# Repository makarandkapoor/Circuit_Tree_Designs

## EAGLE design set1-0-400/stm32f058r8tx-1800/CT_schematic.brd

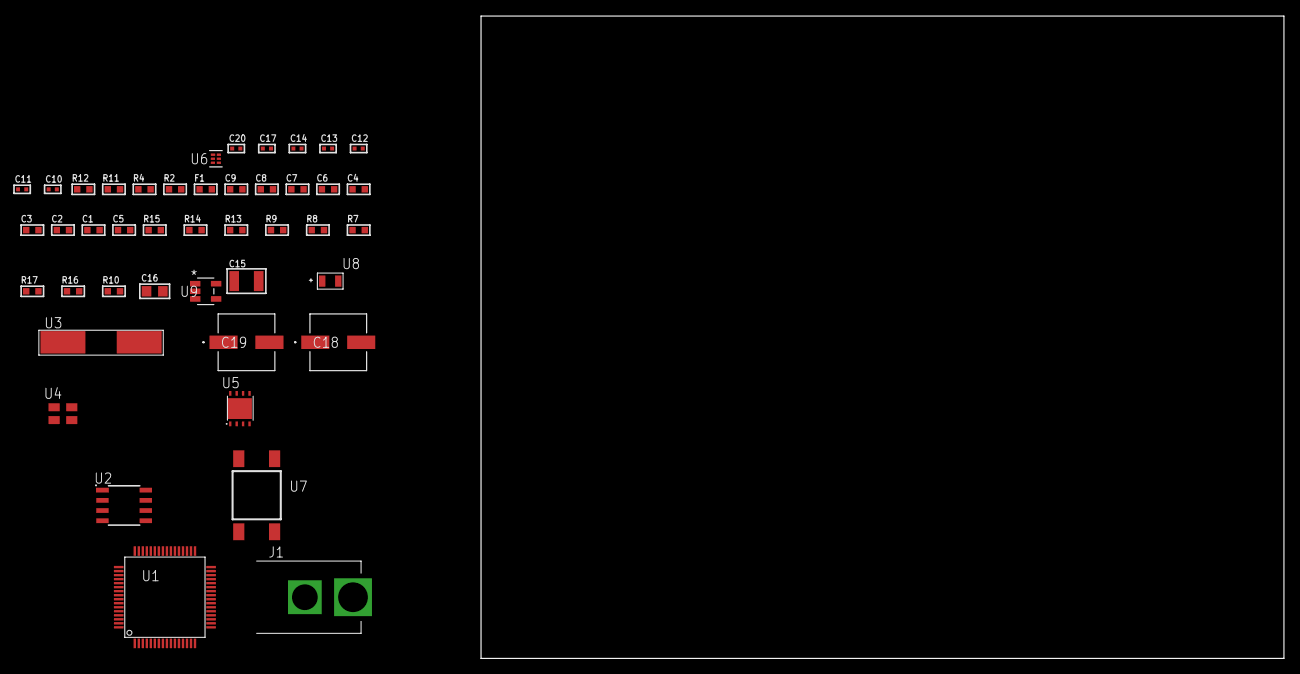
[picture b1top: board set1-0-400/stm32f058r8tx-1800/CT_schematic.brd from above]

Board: 2 copper layers, 100.0 x 80.0 mm, 44 parts (0 on the bottom side), 19 nets, no tracks yet.

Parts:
C1, C9: 1e-06; C0603
C2, C3, C4, C6, C7: 1e-07; C0603
C5: 4.7e-06; C0603
C8: 1e-08; C0603
C10, C11: 1e-11; C0402
C12, C13, C14, C20: 1e-08; C0402
C15: 1e-05; C1210
C16: 1e-05; C0805
C17: 1e-07; C0402
C18, C19: 0.0001; EXV-9H
F1: 240.0; L0603
J1: PJ-037B; PJ-037B_PACKAGE
R2, R12: 1000.0; R0603
R4: 4700.0; R0603
R7, R8, R9, R13, R14: 10000.0; R0603
R10: 100000.0; R0603
R11: 806.0; R0603
R15: 82000.0; R0603
R16: 300000.0; R0603
R17: 120000.0; R0603
U1: stm32f058r8t7; LQFP64
U2: M24M02-DRMN6TP; SOIC-8
U3: ABLS-25.000MHZ-B2F-T
U4: ASEK-2-32.768KHz-ECST; ASEK
U5: LP3878SDX-ADJ/NOPB; WSON-8
U6: TPS3895ADRYR; SON-6
U7: 4-1437565-2; SW_4-1437565-2
U8: Q65110A2395; LGM67K-G1J2-24-Z
U9: nc7sz125m5x; NC7SZ125M5X

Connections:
CLK_CRYSTAL_U1_5: C10.1, U1.5, U3.1
CLK_CRYSTAL_U1_6: C11.1, U1.6, U3.2
CLK_U1_3: U1.3, U4.3
GND: C1.2, C2.2, C3.2, C4.2, C5.2, C6.2, C7.2, C8.2, C9.2, C10.2, C11.2, C12.2, C13.2, C14.2, C15.2, C16.2, C17.2, C18.2, C19.2, C20.2, J1.2, R2.2, R7.2, R8.2, R9.2, R12.2, R15.2, R17.2, U1.12, U1.31, U1.63, U2.4, U4.2, U5.3, U5.PAD, U6.2, U8.C, U9.1, U9.3
NET_U1_7: R4.1, U1.7, U9.4
NET_U1_13: C8.1, C9.1, F1.1, U1.13
NET_U1_28: R8.1, U1.28
NET_U1_60: R7.1, U1.60
NET_U1_62: U7.3, U7.4
NET_U2_3: R9.1, U2.3
NET_U5_1: C14.1, U5.1
NET_U5_6: R11.2, R12.1, U5.6
NET_U5_8: R10.1, U5.8
NET_U6_1: R14.1, R15.1, U6.1
NET_U6_3: R16.2, R17.1, U6.3
NET_U6_4: R13.1, U6.4, U9.2
NET_U7_1: R2.1, U7.1, U7.2
VCC_S1_13V7: C15.1, C18.1, C19.1, J1.1, R10.2, U5.4
VCC_TIER1_1V8: C1.1, C2.1, C3.1, C4.1, C5.1, C6.1, C7.1, C12.1, C13.1, C16.1, C17.1, C20.1, F1.2, R4.2, R11.1, R13.2, R14.2, R16.1, U1.1, U1.32, U1.64, U2.8, U4.4, U5.5, U6.6, U9.5

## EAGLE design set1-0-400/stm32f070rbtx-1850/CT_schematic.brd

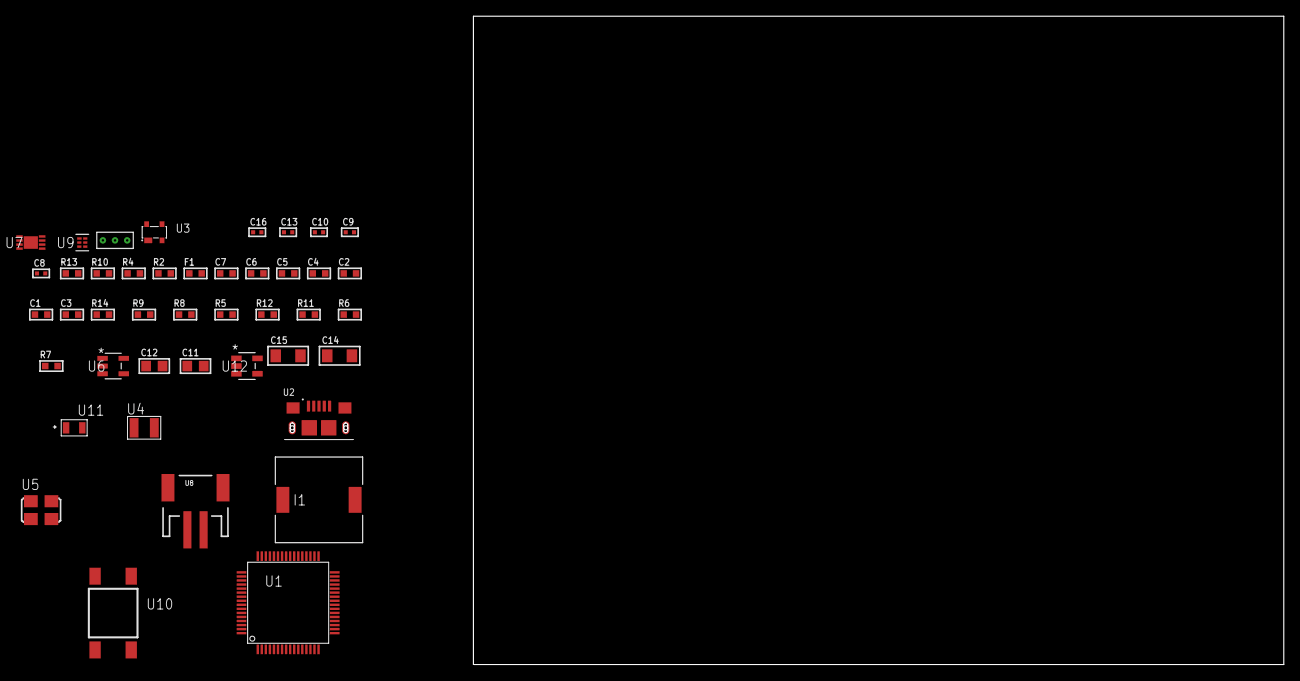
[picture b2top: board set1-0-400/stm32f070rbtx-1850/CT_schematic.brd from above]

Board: 2 copper layers, 122.6 x 80.0 mm, 43 parts (0 on the bottom side), 24 nets, no tracks yet.

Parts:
C1, C2, C4, C5: 1e-07; C0603
C3: 4.7e-06; C0603
C6: 1e-08; C0603
C7: 1e-06; C0603
C8, C9: 1e-11; C0402
C10, C16: 1e-08; C0402
C11, C12: 1e-05; C0805
C13: 1e-07; C0402
C14, C15: 1e-05; C1206
F1: 240.0; L0603
I1: 2.5e-06; DR1040
R2: 1000.0; R0603
R4: 4700.0; R0603
R5, R8, R9, R14: 10000.0; R0603
R6: 220000.0; R0603
R7: 1000000.0; R0603
R10: 9100.0; R0603
R11: 680000.0; R0603
R12: 120000.0; R0603
R13: 2000.0; R0603
U1: stm32f070rbt7; LQFP64
U2: 10118193-0001LF; FCI_10118193-0001LF
U3: prtr5v0u2ax; SOT143B
U4: ABS07-32.768KHZ-7-T
U5: ASFL1-25MHZ-NCS; ASFL1
U6: ltc3406es5; TSOT-23-5
U7: MCP73831T-2ACI/MC; DFN8_2X3MC
U8: S2B-PH-SM4-TB(LF)(SN); JST-2-SMD
U9: TPS3895ADRYR; SON-6
U10: 4-1437565-2; SW_4-1437565-2
U11: Q65110A2395; LGM67K-G1J2-24-Z
U12: nc7sz125m5x; NC7SZ125M5X
U13: Dummy; DUMMY_PACKAGE_90

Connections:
CLK_CRYSTAL_U1_3: C8.1, U1.3, U4.1
CLK_CRYSTAL_U1_4: C9.1, U1.4, U4.2
CLK_U1_5: U1.5, U5.3
GND: C1.2, C2.2, C3.2, C4.2, C5.2, C6.2, C7.2, C8.2, C9.2, C10.2, C11.2, C12.1, C12.2, C13.2, C14.2, C15.2, C16.2, R2.2, R5.2, R6.2, R10.2, R12.2, R13.2, U1.12, U1.18, U1.31, U1.47, U1.63, U2.5, U2.6, U2.7, U2.8, U2.9, U3.1, U5.2, U6.2, U7.6, U7.9, U8.2, U9.2, U11.C, U12.1, U12.3, U13.1
INPUT_USBPOWER_5V: C14.1, R14.2, U2.1, U3.4, U7.1, U7.2
NET_U1_7: R4.1, U1.7, U12.4
NET_U1_13: C6.1, C7.1, F1.1, U1.13
NET_U1_60: R5.1, U1.60
NET_U1_62: U10.3, U10.4
NET_U6_3: I1.1, U6.3
NET_U6_5: R6.1, R7.1, U6.5
NET_U6_ATNET_3: I1.2, R7.2
NET_U7_5: R14.1, U7.5
NET_U7_8: R13.1, U7.8
NET_U9_1: R9.1, R10.1, U9.1
NET_U9_3: R11.2, R12.1, U9.3
NET_U9_4: R8.1, U9.4, U12.2
NET_U10_1: R2.1, U10.1, U10.2
PROC_ADC_IN0: U1.14, U13.2
PROC_ADC_IN1: U1.15, U13.3
PROC_USB_DM: U1.44, U2.2, U3.3
PROC_USB_DP: U1.45, U2.3, U3.2
VCC_S1_3V7: C11.1, C15.1, U6.4, U7.3, U7.4, U8.1
VCC_TIER1_3V3: C1.1, C2.1, C3.1, C4.1, C5.1, C10.1, C12.2, C13.1, C16.1, F1.2, I1.2, R4.2, R7.2, R8.2, R9.2, R11.1, U1.1, U1.19, U1.32, U1.48, U1.64, U5.4, U9.6, U12.5

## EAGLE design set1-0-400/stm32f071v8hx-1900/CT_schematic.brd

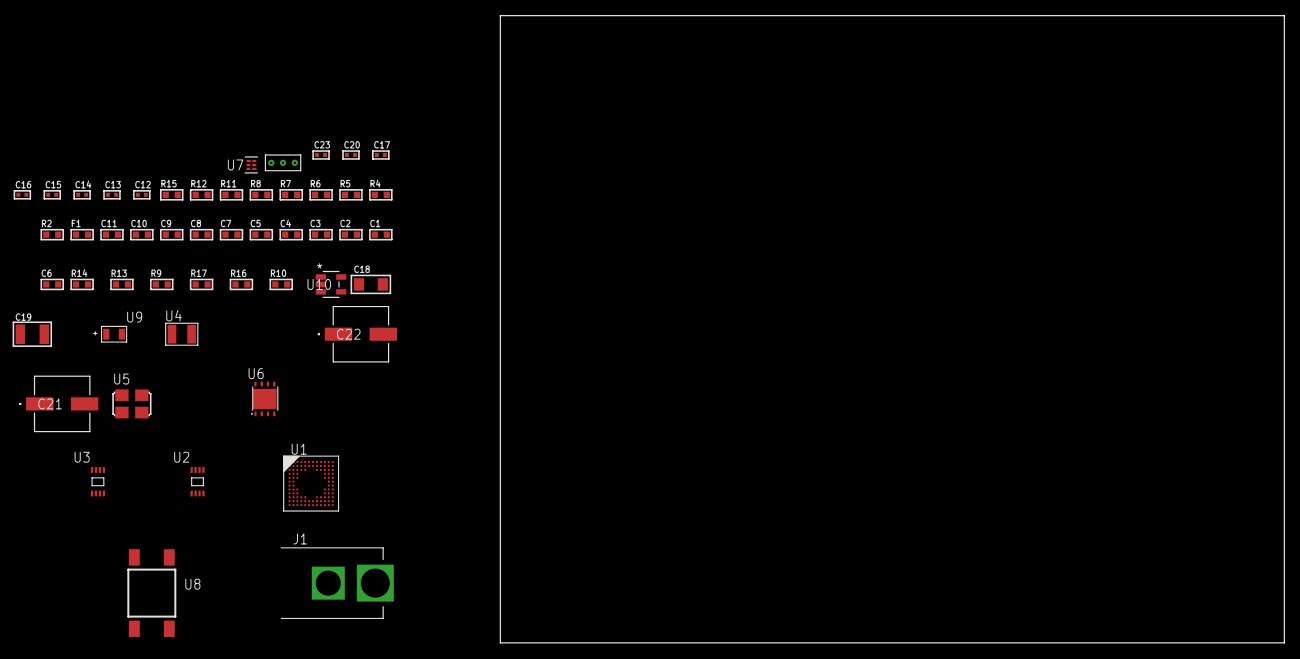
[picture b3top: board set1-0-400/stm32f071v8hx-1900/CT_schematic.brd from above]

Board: 2 copper layers, 100.0 x 80.0 mm, 51 parts (0 on the bottom side), 23 nets, no tracks yet.

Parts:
C1, C11: 1e-06; C0603
C2, C3, C4, C5, C7, C8, C9: 1e-07; C0603
C6: 4.7e-06; C0603
C10: 1e-08; C0603
C12, C13: 1e-11; C0402
C14, C15, C16, C17, C23: 1e-08; C0402
C18: 1e-05; C1206
C19: 1e-05; C1210
C20: 1e-07; C0402
C21, C22: 0.0001; EXV-9H
F1: 240.0; L0603
J1: PJ-037B; PJ-037B_PACKAGE
R2, R12: 1000.0; R0603
R4: 4700.0; R0603
R5, R6, R7, R8: 2200.0; R0603
R9, R13, R14: 10000.0; R0603
R10: 100000.0; R0603
R11: 2231.0; R0603
R15: 9100.0; R0603
R16: 680000.0; R0603
R17: 120000.0; R0603
U1: stm32f071v8h6; UFBGA100
U2: 24AA01T-I/MNY; TDFN-8/6MM
U3: 24AA04-I/MC; TDFN-8/6MM
U4: ABS07-32.768KHZ-7-T
U5: ASFL1-25MHZ-NCS; ASFL1
U6: LP3878SDX-ADJ/NOPB; WSON-8
U7: TPS3895ADRYR; SON-6
U8: 4-1437565-2; SW_4-1437565-2
U9: Q65110A2395; LGM67K-G1J2-24-Z
U10: nc7sz125m5x; NC7SZ125M5X
U11: Dummy; DUMMY_PACKAGE_112

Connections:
CLK_CRYSTAL_U1_D1: C12.1, U1.D1, U4.1
CLK_CRYSTAL_U1_E1: C13.1, U1.E1, U4.2
CLK_U1_F1: U1.F1, U5.3
GND: C1.2, C2.2, C3.2, C4.2, C5.2, C6.2, C7.2, C8.2, C9.2, C10.2, C11.2, C12.2, C13.2, C14.2, C15.2, C16.2, C17.2, C18.2, C19.2, C20.2, C21.2, C22.2, C23.2, J1.2, R2.2, R9.2, R12.2, R15.2, R17.2, U1.D3, U1.F11, U1.F12, U1.K1, U2.4, U3.4, U3.7, U5.2, U6.3, U6.PAD, U7.2, U9.C, U10.1, U10.3, U11.1
NET_U1_A3: R5.1, U1.A3, U2.6
NET_U1_A4: R9.1, U1.A4
NET_U1_B3: R6.1, U1.B3, U2.5
NET_U1_H2: R4.1, U1.H2, U10.4
NET_U1_K11: R8.1, U1.K11, U3.5
NET_U1_K12: R7.1, U1.K12, U3.6
NET_U1_M1: C10.1, C11.1, F1.1, U1.M1
NET_U1_M12: U8.3, U8.4
NET_U6_1: C17.1, U6.1
NET_U6_6: R11.2, R12.1, U6.6
NET_U6_8: R10.1, U6.8
NET_U7_1: R14.1, R15.1, U7.1
NET_U7_3: R16.2, R17.1, U7.3
NET_U7_4: R13.1, U7.4, U10.2
NET_U8_1: R2.1, U8.1, U8.2
PROC_TIM1_CH2: U1.D10, U11.2
PROC_TIM1_CH4: U1.B12, U11.3
VCC_S1_11V0: C18.1, C21.1, C22.1, J1.1, R10.2, U6.4
VCC_TIER1_3V3: C1.1, C2.1, C3.1, C4.1, C5.1, C6.1, C7.1, C8.1, C9.1, C14.1, C15.1, C16.1, C19.1, C20.1, C23.1, F1.2, R4.2, R5.2, R6.2, R7.2, R8.2, R11.1, R13.2, R14.2, R16.1, U1.C4, U1.E2, U1.G11, U1.G12, U1.H3, U2.7, U2.8, U3.8, U5.4, U6.5, U7.6, U10.5

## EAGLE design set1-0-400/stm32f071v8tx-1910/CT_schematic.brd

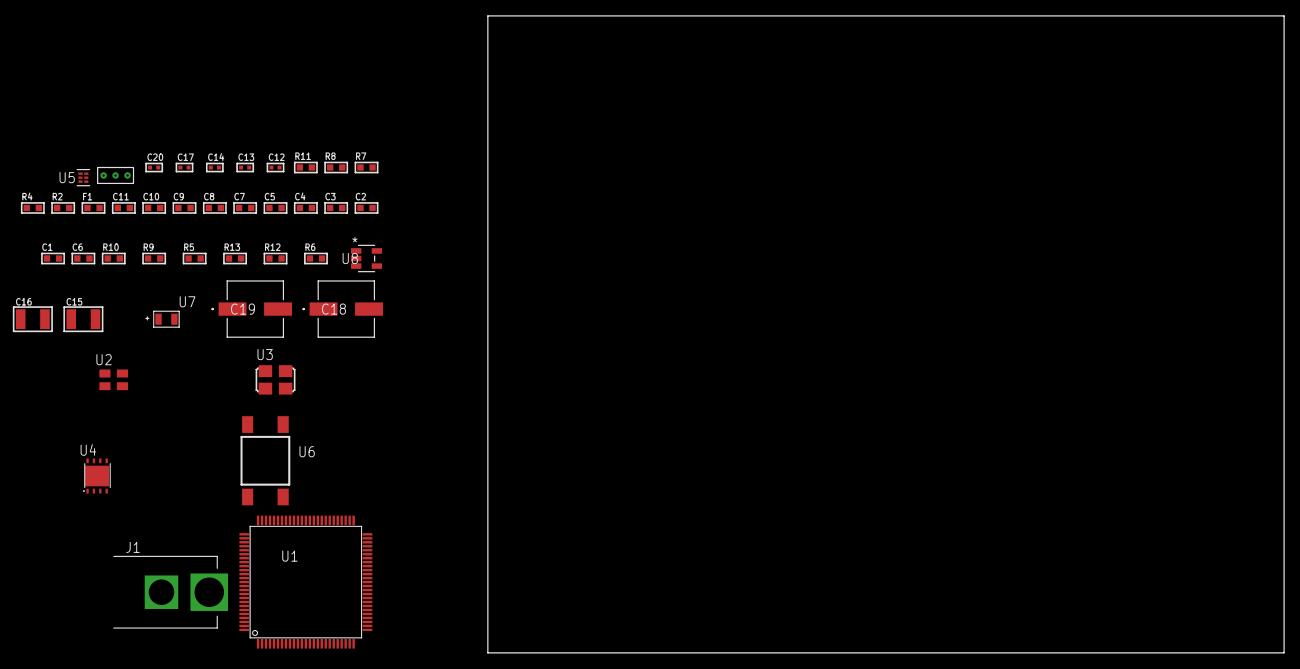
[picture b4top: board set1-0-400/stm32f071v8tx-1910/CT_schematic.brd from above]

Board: 2 copper layers, 100.0 x 80.0 mm, 42 parts (0 on the bottom side), 18 nets, no tracks yet.

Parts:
C1, C11: 1e-06; C0603
C2, C3, C4, C5, C7, C8, C9: 1e-07; C0603
C6: 4.7e-06; C0603
C10: 1e-08; C0603
C12, C13, C14, C20: 1e-08; C0402
C15, C16: 1e-05; C1210
C17: 1e-07; C0402
C18, C19: 0.0001; EXV-9H
F1: 240.0; L0603
J1: PJ-037B; PJ-037B_PACKAGE
R2, R8: 1000.0; R0603
R4: 4700.0; R0603
R5, R9, R10: 10000.0; R0603
R6: 100000.0; R0603
R7: 2231.0; R0603
R11: 9100.0; R0603
R12: 680000.0; R0603
R13: 120000.0; R0603
U1: stm32f071v8t6; LQFP100
U2: ASEK-32.768KHz-ECST; ASEK
U3: ASFL1-25MHZ-NCS; ASFL1
U4: LP3878SDX-ADJ/NOPB; WSON-8
U5: TPS3895ADRYR; SON-6
U6: 4-1437565-2; SW_4-1437565-2
U7: Q65110A2395; LGM67K-G1J2-24-Z
U8: nc7sz125m5x; NC7SZ125M5X
U9: Dummy; DUMMY_PACKAGE_89

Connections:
CLK_U1_8: U1.8, U2.3
CLK_U1_12: U1.12, U3.3
GND: C1.2, C2.2, C3.2, C4.2, C5.2, C6.2, C7.2, C8.2, C9.2, C10.2, C11.2, C12.2, C13.2, C14.2, C15.2, C16.2, C17.2, C18.2, C19.2, C20.2, J1.2, R2.2, R5.2, R8.2, R11.2, R13.2, U1.20, U1.27, U1.49, U1.74, U1.99, U2.2, U3.2, U4.3, U4.PAD, U5.2, U7.C, U8.1, U8.3, U9.1
NET_U1_14: R4.1, U1.14, U8.4
NET_U1_21: C10.1, C11.1, F1.1, U1.21
NET_U1_94: R5.1, U1.94
NET_U1_98: U6.3, U6.4
NET_U4_1: C14.1, U4.1
NET_U4_6: R7.2, R8.1, U4.6
NET_U4_8: R6.1, U4.8
NET_U5_1: R10.1, R11.1, U5.1
NET_U5_3: R12.2, R13.1, U5.3
NET_U5_4: R9.1, U5.4, U8.2
NET_U6_1: R2.1, U6.1, U6.2
PROC_PE2: U1.1, U9.2
PROC_PE3: U1.2, U9.3
VCC_S1_13V4: C15.1, C18.1, C19.1, J1.1, R6.2, U4.4
VCC_TIER1_3V3: C1.1, C2.1, C3.1, C4.1, C5.1, C6.1, C7.1, C8.1, C9.1, C12.1, C13.1, C16.1, C17.1, C20.1, F1.2, R4.2, R7.1, R9.2, R10.2, R12.1, U1.6, U1.28, U1.50, U1.75, U1.100, U2.4, U3.4, U4.5, U5.6, U8.5

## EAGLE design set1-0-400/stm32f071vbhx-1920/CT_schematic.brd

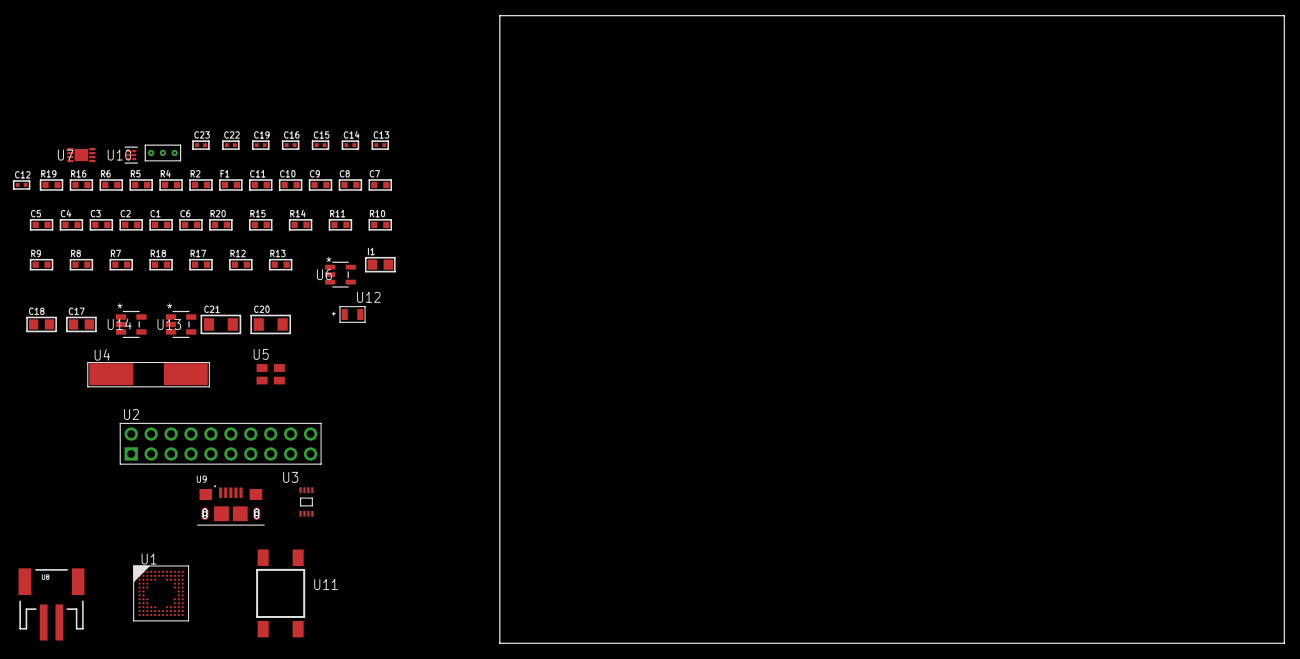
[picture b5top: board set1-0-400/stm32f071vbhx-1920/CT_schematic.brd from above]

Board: 2 copper layers, 58 parts (0 on the bottom side), 30 nets, no tracks yet.

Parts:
C1, C11: 1e-06; C0603
C2, C3, C4, C5, C7, C8, C9: 1e-07; C0603
C6: 4.7e-06; C0603
C10: 1e-08; C0603
C12, C13: 1e-11; C0402
C14, C19: 1e-07; C0402
C15, C16, C22, C23: 1e-08; C0402
C17, C18: 1e-05; C0805
C20, C21: 1e-05; C1206
F1: 240.0; L0603
I1: 2.2e-06; L0805
R2: 1000.0; R0603
R4: 4700.0; R0603
R5, R6: 2200.0; R0603
R7, R8, R9, R10, R11, R14, R15, R20: 10000.0; R0603
R12: 220000.0; R0603
R13: 1000000.0; R0603
R16: 9100.0; R0603
R17: 680000.0; R0603
R18: 120000.0; R0603
R19: 2000.0; R0603
U1: stm32f071vbh7; UFBGA100
U2: TST-110-05-T-D-RA
U3: 24AA128T-I/MNY; TDFN-8/6MM
U4: ABLS-25.000MHZ-B2F-T
U5: ASEK-32.768KHz-ECST; ASEK
U6: ltc3406es5; TSOT-23-5
U7: MCP73831T-2ACI/MC; DFN8_2X3MC
U8: S2B-PH-SM4-TB(LF)(SN); JST-2-SMD
U9: 10118193-0001LF; FCI_10118193-0001LF
U10: TPS3895ADRYR; SON-6
U11: 4-1437565-2; SW_4-1437565-2
U12: Q65110A2395; LGM67K-G1J2-24-Z
U13, U14: nc7sz125m5x; NC7SZ125M5X
U15: Dummy; DUMMY_PACKAGE_128

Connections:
CLK_CRYSTAL_U1_F1: C12.1, U1.F1, U4.1
CLK_CRYSTAL_U1_G1: C13.1, U1.G1, U4.2
CLK_U1_D1: U1.D1, U5.3
GND: C1.2, C2.2, C3.2, C4.2, C5.2, C6.2, C7.2, C8.2, C9.2, C10.2, C11.2, C12.2, C13.2, C14.2, C15.2, C16.2, C17.2, C18.1, C18.2, C19.2, C20.2, C21.2, C22.2, C23.2, R2.2, R7.2, R9.2, R10.2, R12.2, R16.2, R18.2, R19.2, U1.D3, U1.F11, U1.F12, U1.K1, U2.4, U2.6, U2.8, U2.10, U2.12, U2.14, U2.16, U2.18, U2.20, U3.4, U3.7, U5.2, U6.2, U7.6, U7.9, U8.2, U9.5, U9.6, U9.7, U9.8, U9.9, U10.2, U12.C, U13.2, U13.3, U14.1, U14.3, U15.1
INPUT_USBPOWER_5V: C20.1, R20.2, U7.1, U7.2, U9.1
NET_U1_A3: R5.1, U1.A3, U3.6
NET_U1_A4: R7.1, U1.A4
NET_U1_B3: R6.1, U1.B3, U3.5
NET_U1_H2: R4.1, U1.H2, U14.4
NET_U1_M1: C10.1, C11.1, F1.1, U1.M1
NET_U1_M12: U11.3, U11.4
NET_U3_1: R9.1, U3.1
NET_U3_2: R10.1, U3.2
NET_U3_3: R11.1, U3.3
NET_U6_3: I1.1, U6.3
NET_U6_5: R12.1, R13.1, U6.5
NET_U6_ATNET_3: I1.2, R13.2
NET_U7_5: R20.1, U7.5
NET_U7_8: R19.1, U7.8
NET_U10_1: R15.1, R16.1, U10.1
NET_U10_3: R17.2, R18.1, U10.3
NET_U10_4: R14.1, U10.4, U13.4, U14.2
NET_U11_1: R2.1, U11.1, U11.2
PROC_SYS_SWCLK: U1.A10, U2.9
PROC_SYS_SWDIO: U1.A11, U2.7
PROC_TIM1_CH2: U1.D10, U15.2
PROC_TIM1_CH4: U1.B12, U15.3
RST_OUT_U2_SRESET_B: R8.1, U2.15, U13.1
VCC_S1_3V7: C17.1, C21.1, U6.4, U7.3, U7.4, U8.1
VCC_TIER1_3V3: C1.1, C2.1, C3.1, C4.1, C5.1, C6.1, C7.1, C8.1, C9.1, C14.1, C15.1, C16.1, C18.2, C19.1, C22.1, C23.1, F1.2, I1.2, R4.2, R5.2, R6.2, R8.2, R11.2, R13.2, R14.2, R15.2, R17.1, U1.C4, U1.E2, U1.G11, U1.G12, U1.H3, U2.1, U3.8, U5.4, U10.6, U13.5, U14.5

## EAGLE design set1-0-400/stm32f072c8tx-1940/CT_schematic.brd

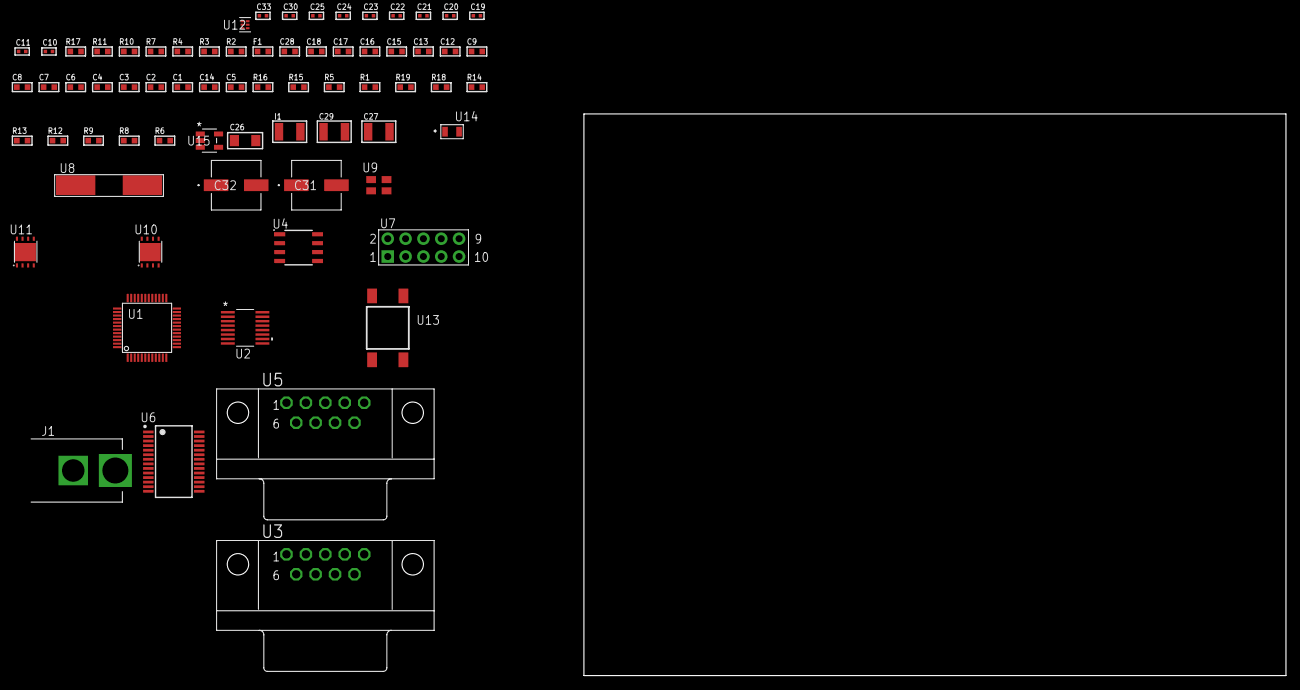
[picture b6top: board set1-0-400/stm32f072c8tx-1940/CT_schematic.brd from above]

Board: 2 copper layers, 100.0 x 80.0 mm, 70 parts (0 on the bottom side), 55 nets, no tracks yet.

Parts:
C1, C9, C12, C13, C15, C16, C17, C18, C28: 1e-06; C0603
C2, C3, C4, C6, C7: 1e-07; C0603
C5: 4.7e-06; C0603
C8: 1e-08; C0603
C10, C11: 1e-11; C0402
C14: 2.2e-07; C0603
C19, C20, C21, C22, C23, C30: 1e-07; C0402
C24, C25, C33: 1e-08; C0402
C26: 1e-05; C1206
C27, C29: 1e-05; C1210
C31, C32: 0.0001; EXV-9H
F1: 240.0; L0603
I1: 1e-05; L1210
J1: PJ-037B; PJ-037B_PACKAGE
R1, R5, R15, R16: 10000.0; R0603
R2, R11: 1000.0; R0603
R3: 1600.5; R0603
R4: 4700.0; R0603
R6, R8, R9, R12, R14: 100000.0; R0603
R7: 120.0; R0603
R10: 2231.0; R0603
R13: 300000.0; R0603
R17: 9100.0; R0603
R18: 680000.0; R0603
R19: 120000.0; R0603
U1: stm32f072c8t7; LQFP48
U2: LTC2804CGN-1#PBF; SSOP-16
U3, U5: 182-009-113R531; 182-009-MALE
U4: MCP2562-E/SN; SOIC-8
U6: ST3241EBPR; SSOP-28
U7: HTSS-105-01-G-D
U8: ABLS-25.000MHZ-B2F-T
U9: ASEK-32.768KHz-ECST; ASEK
U10: LP3878SDX-ADJ/NOPB; WSON-8
U11: LP2951ACSDX/NOPB; WSON-8
U12: TPS3895ADRYR; SON-6
U13: 4-1437565-2; SW_4-1437565-2
U14: Q65110A2395; LGM67K-G1J2-24-Z
U15: nc7sz125m5x; NC7SZ125M5X

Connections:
CLK_CRYSTAL_U1_5: C10.1, U1.5, U8.1
CLK_CRYSTAL_U1_6: C11.1, U1.6, U8.2
CLK_U1_3: U1.3, U9.3
GND: C1.2, C2.2, C3.2, C4.2, C5.2, C6.2, C7.2, C8.2, C9.2, C10.2, C11.2, C12.2, C13.2, C15.2, C16.2, C17.2, C18.2, C19.2, C22.2, C23.2, C24.2, C25.2, C26.2, C27.2, C28.2, C29.2, C30.2, C31.2, C32.2, C33.2, J1.2, R2.2, R5.2, R11.2, R14.2, R17.2, R19.2, U1.8, U1.23, U1.35, U1.47, U2.8, U3.5, U4.2, U4.8, U5.5, U6.23, U6.25, U7.9, U9.2, U10.3, U10.PAD, U11.3, U11.4, U11.PAD, U12.2, U14.C, U15.1, U15.3
NET_U1_7: R4.1, U1.7, U15.4
NET_U1_9: C8.1, C9.1, F1.1, U1.9
NET_U1_36: C7.1, U1.36
NET_U1_42: R3.1, U1.42, U14.A
NET_U1_43: R1.1, U1.43, U13.3, U13.4
NET_U1_44: R5.1, U1.44
NET_U2_6: C12.1, U2.6
NET_U2_7: C14.1, I1.2, U2.7
NET_U2_9: C13.1, U2.9
NET_U2_10: C14.2, U2.10
NET_U2_11: R6.1, U2.11
NET_U3_2: U2.1, U3.2
NET_U3_3: U2.3, U3.3
NET_U3_7: U2.2, U3.7
NET_U3_8: U2.4, U3.8
NET_U4_6: R7.2, U4.6
NET_U5_2: R7.2, U4.6, U5.2
NET_U5_3: R7.1, U4.7, U5.3
NET_U6_1: C21.1, U6.1
NET_U6_2: C21.2, U6.2
NET_U6_3: C23.1, U6.3
NET_U6_22: R8.1, U6.22
NET_U6_24: C20.2, U6.24
NET_U6_27: C22.1, U6.27
NET_U6_28: C20.1, U6.28
NET_U7_3: U6.4, U7.3
NET_U7_4: U6.5, U7.4
NET_U7_5: U6.9, U7.5
NET_U7_6: U6.10, U7.6
NET_U10_1: C25.1, U10.1
NET_U10_6: R10.2, R11.1, U10.6
NET_U10_8: R9.1, U10.8
NET_U11_5: R12.1, U11.5
NET_U11_7: R13.2, R14.1, U11.7
NET_U12_1: R16.1, R17.1, U12.1
NET_U12_3: R18.2, R19.1, U12.3
NET_U12_4: R15.1, U12.4, U15.2
NET_U13_1: R2.1, U13.1, U13.2
PROC_CAN_RX: U1.45, U4.4
PROC_CAN_TX: U1.46, U4.1
PROC_USART1_CTS: U1.32, U6.13
PROC_USART1_RTS: U1.33, U6.18
PROC_USART1_RX: U1.31, U6.19
PROC_USART1_TX: U1.30, U6.14
PROC_USART2_CTS: U1.10, U2.13
PROC_USART2_RTS: U1.11, U2.15
PROC_USART2_RX: U1.13, U2.16
PROC_USART2_TX: U1.12, U2.14
VCC_S1_8V6: C26.1, C28.1, C31.1, C32.1, J1.1, R9.2, U10.4, U11.8
VCC_TIER1_3V3: C1.1, C2.1, C3.1, C4.1, C5.1, C6.1, C15.1, C16.1, C18.1, C19.1, C24.1, C27.1, C30.1, C33.1, F1.2, I1.1, R1.2, R3.2, R4.2, R6.2, R8.2, R10.1, R15.2, R16.2, R18.1, U1.1, U1.24, U1.48, U2.5, U2.12, U4.5, U6.26, U9.4, U10.5, U12.6, U15.5
VCC_TIER1_5V0: C17.1, C29.1, R12.2, R13.1, U4.3, U11.1
